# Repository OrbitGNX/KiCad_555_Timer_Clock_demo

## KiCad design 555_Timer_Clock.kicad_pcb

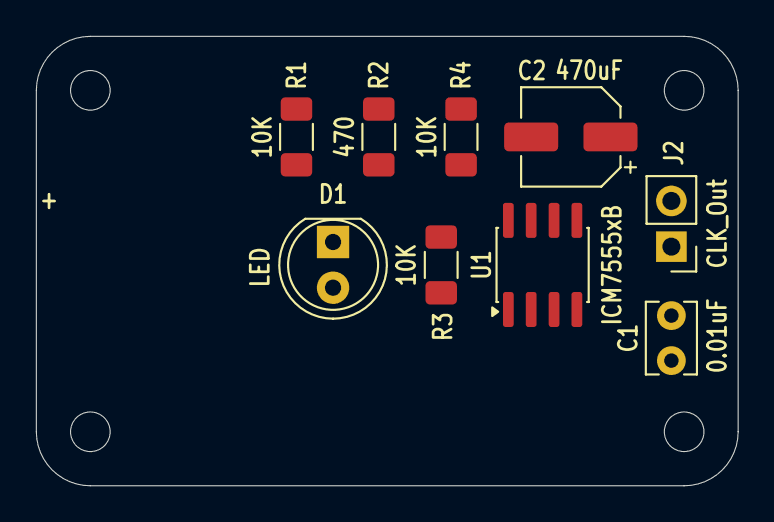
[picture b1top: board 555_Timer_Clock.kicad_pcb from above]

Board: 2 copper layers, 39.0 x 25.0 mm, 13 parts (0 on the bottom side), 8 nets, no tracks yet.

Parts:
C1: 0.01uF; C_Disc_D3.8mm_W2.6mm_P2.50mm
C2: 470uF; CP_Elec_5x5.4
D1: LED; LED_D5.0mm
H1, H2, H3, H4: MountingHole; MountingHole_2.2mm_M2
J2: CLK_Out; PinHeader_1x02_P2.54mm_Vertical
R1, R3, R4: 10K; R_1206_3216Metric_Pad1.30x1.75mm_HandSolder
R2: 470; R_1206_3216Metric_Pad1.30x1.75mm_HandSolder
U1: ICM7555xB; SOIC-8_3.9x4.9mm_P1.27mm

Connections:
/+5V: R1.2, R3.2, R4.2, U1.8 (VCC)
/CLK_Out: D1.2 (A), J2.1, U1.3 (OUT)
/RST: R3.1, U1.4 (~RST)
/Trigger: R1.1, U1.2 (TRIG)
GND: C1.2, C2.2, J2.2, R2.1, U1.1 (GND)
unnamed: D1.1 (K), R2.2
unnamed: C1.1, U1.5 (CONT)
unnamed: C2.1, R4.1, U1.6 (THRES), U1.7 (DISCH)

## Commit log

2026-03-26 Enhance README with project details and objectives
    Expanded the README to include an overview, learning objectives, and circuit description for the 555 Timer Clock project.
2026-03-26 update gyronix logo
2026-03-27 Add Multisim
2026-03-27 add files folder
2026-03-27 add schematic pdf and BOM
